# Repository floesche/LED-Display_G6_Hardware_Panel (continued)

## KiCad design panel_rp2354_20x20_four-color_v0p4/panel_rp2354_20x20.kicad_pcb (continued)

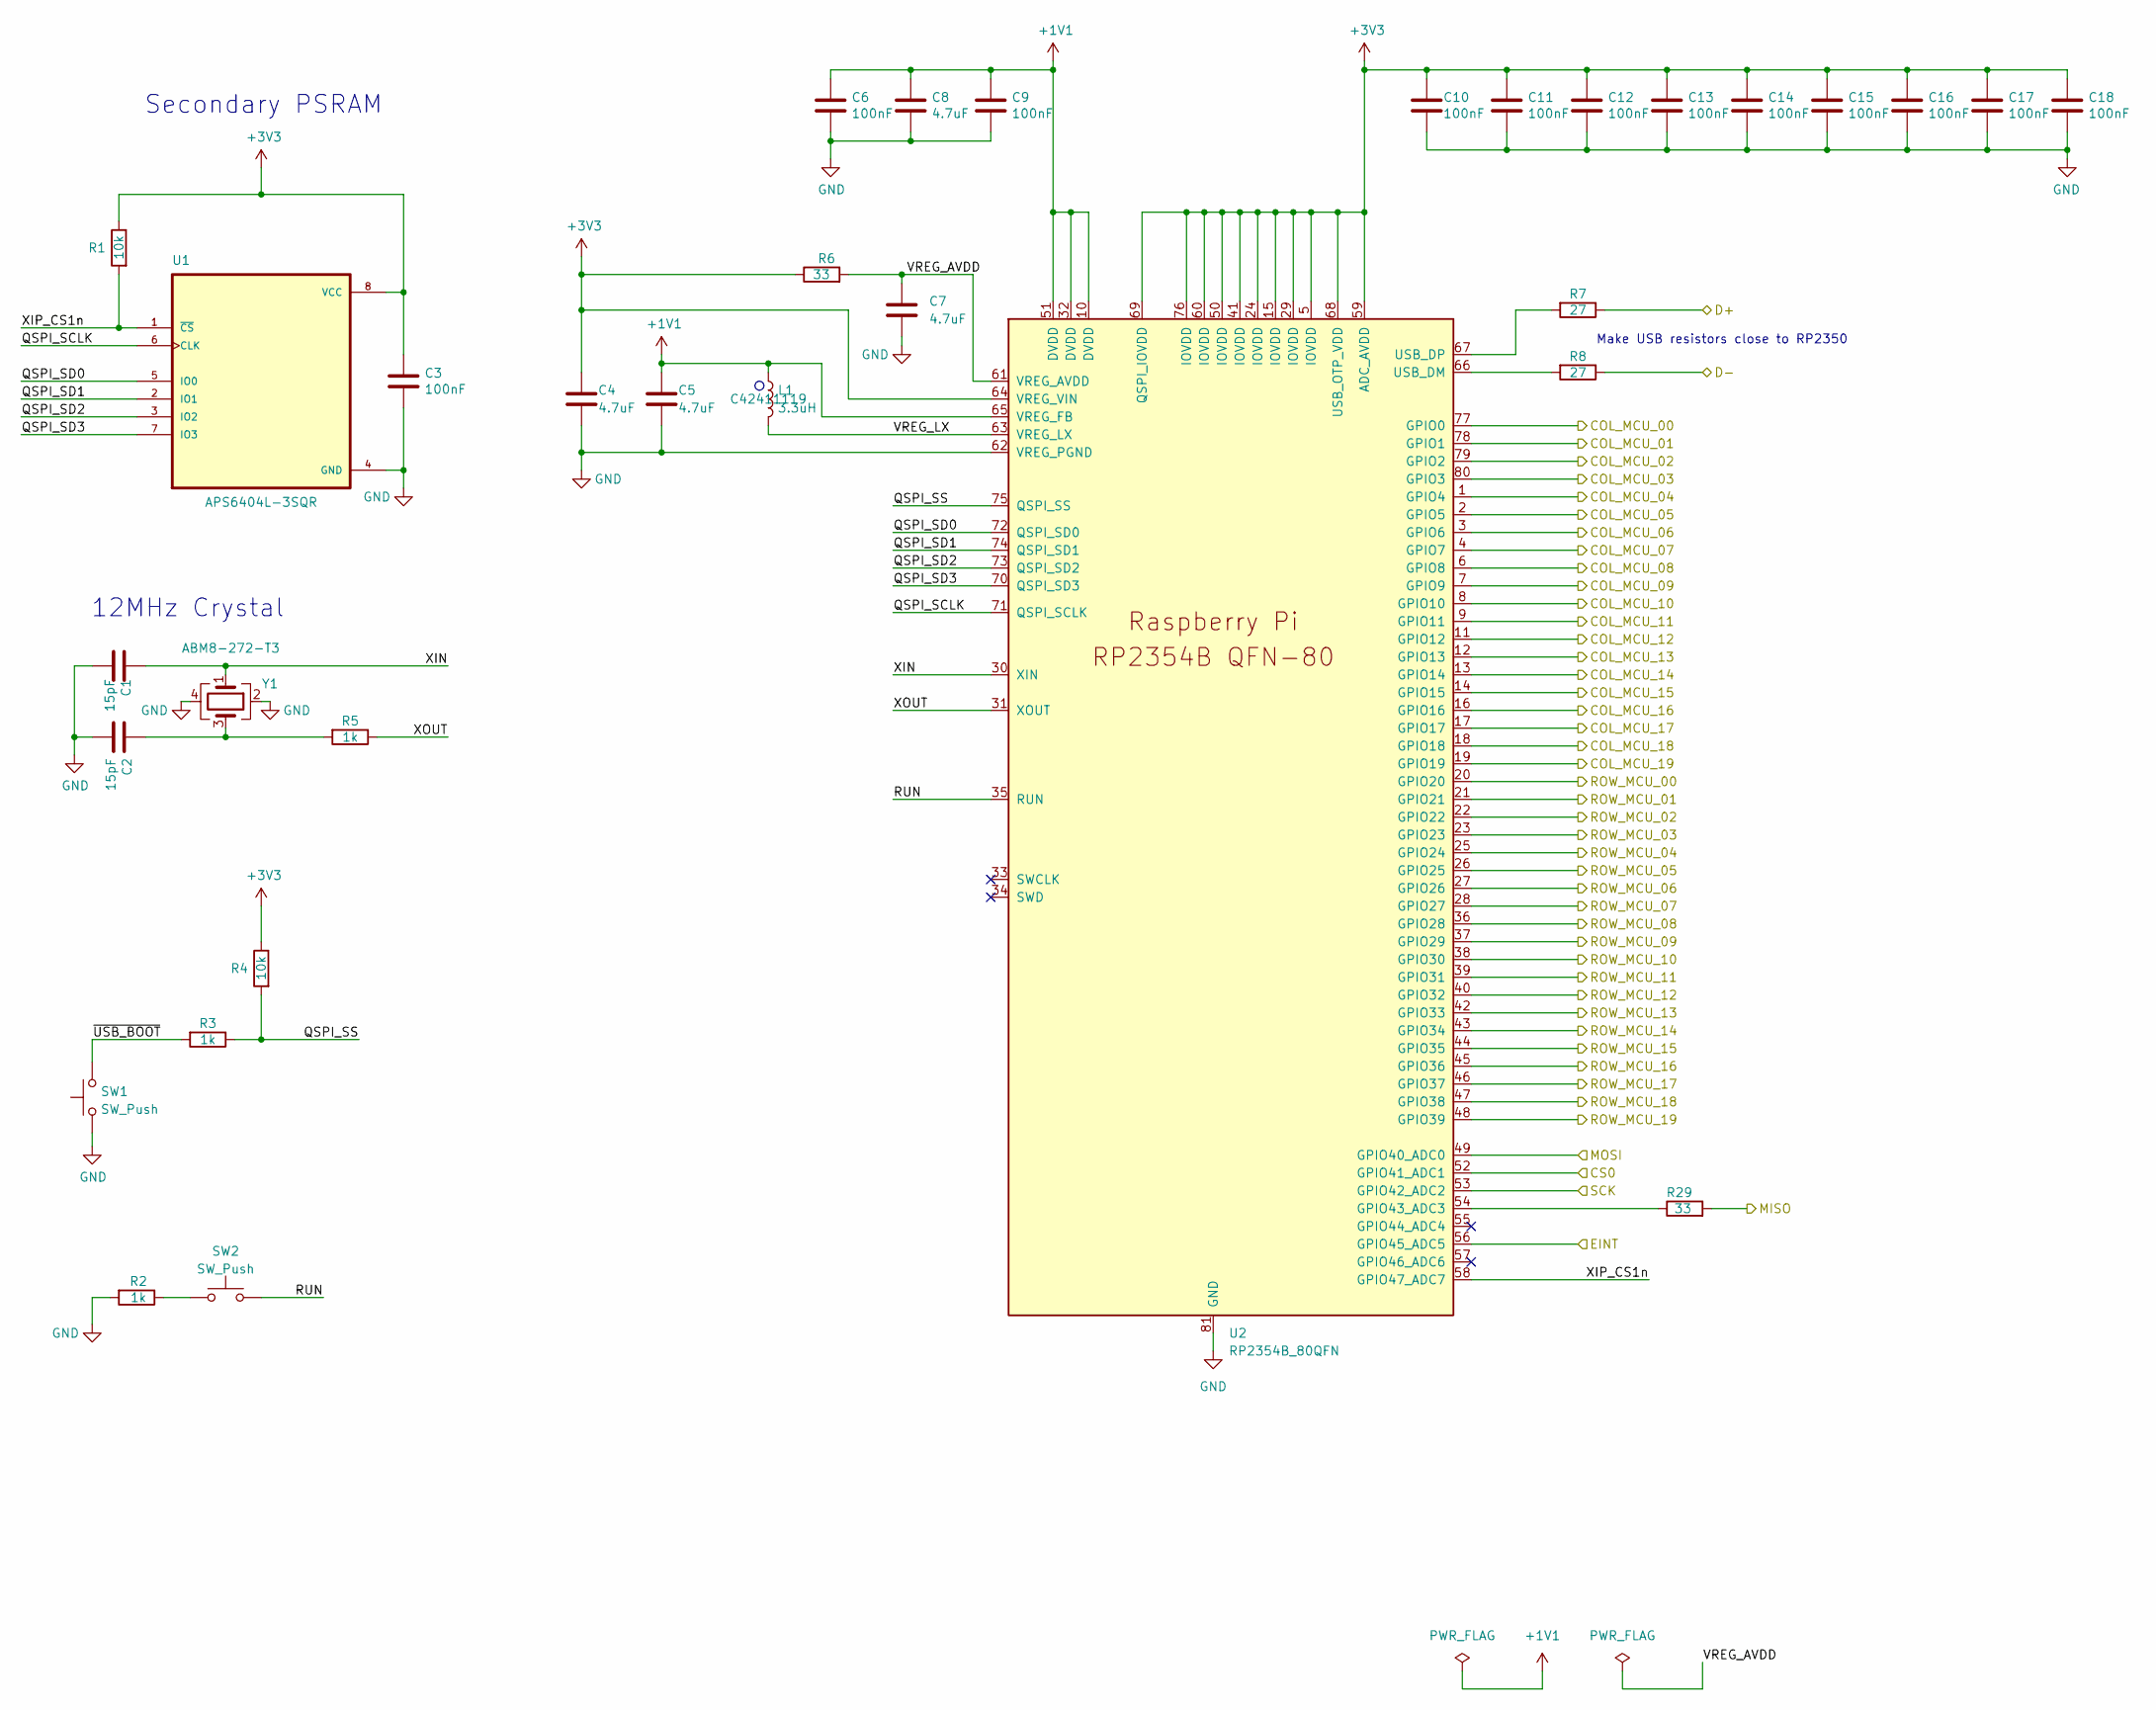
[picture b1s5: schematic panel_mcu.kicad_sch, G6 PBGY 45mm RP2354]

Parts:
C1, C2: 15pF; C_0201_0603Metric; LCSC Part # C541259
C3, C6, C9, C10, C11, C12, C13, C14, C15, C16, C17, C18: 100nF; C_0201_0603Metric; LCSC Part # C76939
C4, C5: 4.7uF; C_0402_1005Metric_small_pads; LCSC Part # C368809
C7, C8: 4.7uF; C_0402_1005Metric; LCSC Part # C368809
L1: 3.3uH; L_pol_2016; LCSC Part # C42411119
R1, R4: 10k; R_0201_0603Metric; LCSC Part # C473048
R2, R3, R5: 1k; R_0201_0603Metric; LCSC Part # C270365
R6, R29: 33; R_0201_0603Metric; LCSC Part # C295794
R7, R8: 27; R_0201_0603Metric; LCSC Part # C473051
SW1, SW2: SW_Push; TS-1088-AR02016; LCSC Part # C720477
U1: APS6404L-3SQR; flashmem_PSON50P300X200X60-9N; LCSC Part # C3040877
U2: RP2354B_80QFN; RP2350-QFN-80-1EP_10x10_P0.4mm_EP3.4x3.4mm_ThermalVias; LCSC Part # C39843328
Y1: ABM8-272-T3; Crystal_SMD_3225-4Pin_3.2x2.5mm; LCSC Part # C20625731

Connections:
+1V1: C5.1, C6.1, C8.1, C9.1, L1.1, U2.10 (DVDD), U2.32 (DVDD), U2.51 (DVDD), U2.65 (VREG_FB)
+3V3: C3.1, C4.1, C10.1, C11.1, C12.1, C13.1, C14.1, C15.1, C16.1, C17.1, C18.1, R1.1, R4.1, R6.1, U1.8 (VCC), U2.5 (IOVDD), U2.15 (IOVDD), U2.24 (IOVDD), U2.29 (IOVDD), U2.41 (IOVDD), U2.50 (IOVDD), U2.59 (ADC_AVDD), U2.60 (IOVDD), U2.64 (VREG_VIN), U2.68 (USB_OTP_VDD), U2.69 (QSPI_IOVDD), U2.76 (IOVDD); also elsewhere on the board
/drivers/COL_MCU_00: U2.77 (GPIO0); also elsewhere on the board
/drivers/COL_MCU_01: U2.78 (GPIO1); also elsewhere on the board
/drivers/COL_MCU_02: U2.79 (GPIO2); also elsewhere on the board
/drivers/COL_MCU_03: U2.80 (GPIO3); also elsewhere on the board
/drivers/COL_MCU_04: U2.1 (GPIO4); also elsewhere on the board
/drivers/COL_MCU_05: U2.2 (GPIO5); also elsewhere on the board
/drivers/COL_MCU_06: U2.3 (GPIO6); also elsewhere on the board
/drivers/COL_MCU_07: U2.4 (GPIO7); also elsewhere on the board
/drivers/COL_MCU_08: U2.6 (GPIO8); also elsewhere on the board
/drivers/COL_MCU_09: U2.7 (GPIO9); also elsewhere on the board
/drivers/COL_MCU_10: U2.8 (GPIO10); also elsewhere on the board
/drivers/COL_MCU_11: U2.9 (GPIO11); also elsewhere on the board
/drivers/COL_MCU_12: U2.11 (GPIO12); also elsewhere on the board
/drivers/COL_MCU_13: U2.12 (GPIO13); also elsewhere on the board
/drivers/COL_MCU_14: U2.13 (GPIO14); also elsewhere on the board
/drivers/COL_MCU_15: U2.14 (GPIO15); also elsewhere on the board
/drivers/COL_MCU_16: U2.16 (GPIO16); also elsewhere on the board
/drivers/COL_MCU_17: U2.17 (GPIO17); also elsewhere on the board
/drivers/COL_MCU_18: U2.18 (GPIO18); also elsewhere on the board
/drivers/COL_MCU_19: U2.19 (GPIO19); also elsewhere on the board
/drivers/ROW_MCU_00: U2.20 (GPIO20); also elsewhere on the board
/drivers/ROW_MCU_01: U2.21 (GPIO21); also elsewhere on the board
/drivers/ROW_MCU_02: U2.22 (GPIO22); also elsewhere on the board
/drivers/ROW_MCU_03: U2.23 (GPIO23); also elsewhere on the board
/drivers/ROW_MCU_04: U2.25 (GPIO24); also elsewhere on the board
/drivers/ROW_MCU_05: U2.26 (GPIO25); also elsewhere on the board
/drivers/ROW_MCU_06: U2.27 (GPIO26); also elsewhere on the board
/drivers/ROW_MCU_07: U2.28 (GPIO27); also elsewhere on the board
/drivers/ROW_MCU_08: U2.36 (GPIO28); also elsewhere on the board
/drivers/ROW_MCU_09: U2.37 (GPIO29); also elsewhere on the board
/drivers/ROW_MCU_10: U2.38 (GPIO30); also elsewhere on the board
/drivers/ROW_MCU_11: U2.39 (GPIO31); also elsewhere on the board
/drivers/ROW_MCU_12: U2.40 (GPIO32); also elsewhere on the board
/drivers/ROW_MCU_13: U2.42 (GPIO33); also elsewhere on the board
/drivers/ROW_MCU_14: U2.43 (GPIO34); also elsewhere on the board
/drivers/ROW_MCU_15: U2.44 (GPIO35); also elsewhere on the board
/drivers/ROW_MCU_16: U2.45 (GPIO36); also elsewhere on the board
/drivers/ROW_MCU_17: U2.46 (GPIO37); also elsewhere on the board
/drivers/ROW_MCU_18: U2.47 (GPIO38); also elsewhere on the board
/drivers/ROW_MCU_19: U2.48 (GPIO39); also elsewhere on the board
/panel_header/CS0: U2.52 (GPIO41_ADC1); also elsewhere on the board
/panel_header/EINT: U2.56 (GPIO45_ADC5); also elsewhere on the board
/panel_header/MISO: R29.2; also elsewhere on the board
/panel_header/MOSI: U2.49 (GPIO40_ADC0); also elsewhere on the board
/panel_header/SCK: U2.53 (GPIO42_ADC2); also elsewhere on the board
/panel_mcu/D+: R7.1; also elsewhere on the board
/panel_mcu/D-: R8.1; also elsewhere on the board
/panel_mcu/QSPI_SCLK: U1.6 (CLK), U2.71 (QSPI_SCLK)
/panel_mcu/QSPI_SD0: U1.5 (IO0), U2.72 (QSPI_SD0)
/panel_mcu/QSPI_SD1: U1.2 (IO1), U2.74 (QSPI_SD1)
/panel_mcu/QSPI_SD2: U1.3 (IO2), U2.73 (QSPI_SD2)
/panel_mcu/QSPI_SD3: U1.7 (IO3), U2.70 (QSPI_SD3)
/panel_mcu/QSPI_SS: R3.1, R4.2, U2.75 (QSPI_SS)
/panel_mcu/RUN: SW2.2, U2.35 (RUN)
/panel_mcu/VREG_AVDD: C7.1, R6.2, U2.61 (VREG_AVDD)
/panel_mcu/VREG_LX: L1.2, U2.63 (VREG_LX)
/panel_mcu/XIN: C1.1, U2.30 (XIN), Y1.1
/panel_mcu/XIP_CS1n: R1.2, U1.1 (~CS), U2.58 (GPIO47_ADC7)
/panel_mcu/XOUT: R5.1, U2.31 (XOUT)
/panel_mcu/~USB_BOOT: R3.2, SW1.2
GND: C1.2, C2.2, C3.2, C4.2, C5.2, C6.2, C7.2, C8.2, C9.2, C10.2, C11.2, C12.2, C13.2, C14.2, C15.2, C16.2, C17.2, C18.2, R2.2, SW1.1, U1.4 (GND), U2.62 (VREG_PGND), U2.81 (GND), Y1.2, Y1.4; also elsewhere on the board
unnamed: C2.1, R5.2, Y1.3
unnamed: R2.1, SW2.1
unnamed: R29.1, U2.54 (GPIO43_ADC3)
unnamed: R8.2, U2.66 (USB_DM)
unnamed: R7.2, U2.67 (USB_DP)

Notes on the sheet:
12MHz Crystal
Secondary PSRAM
Make USB resistors close to RP2350

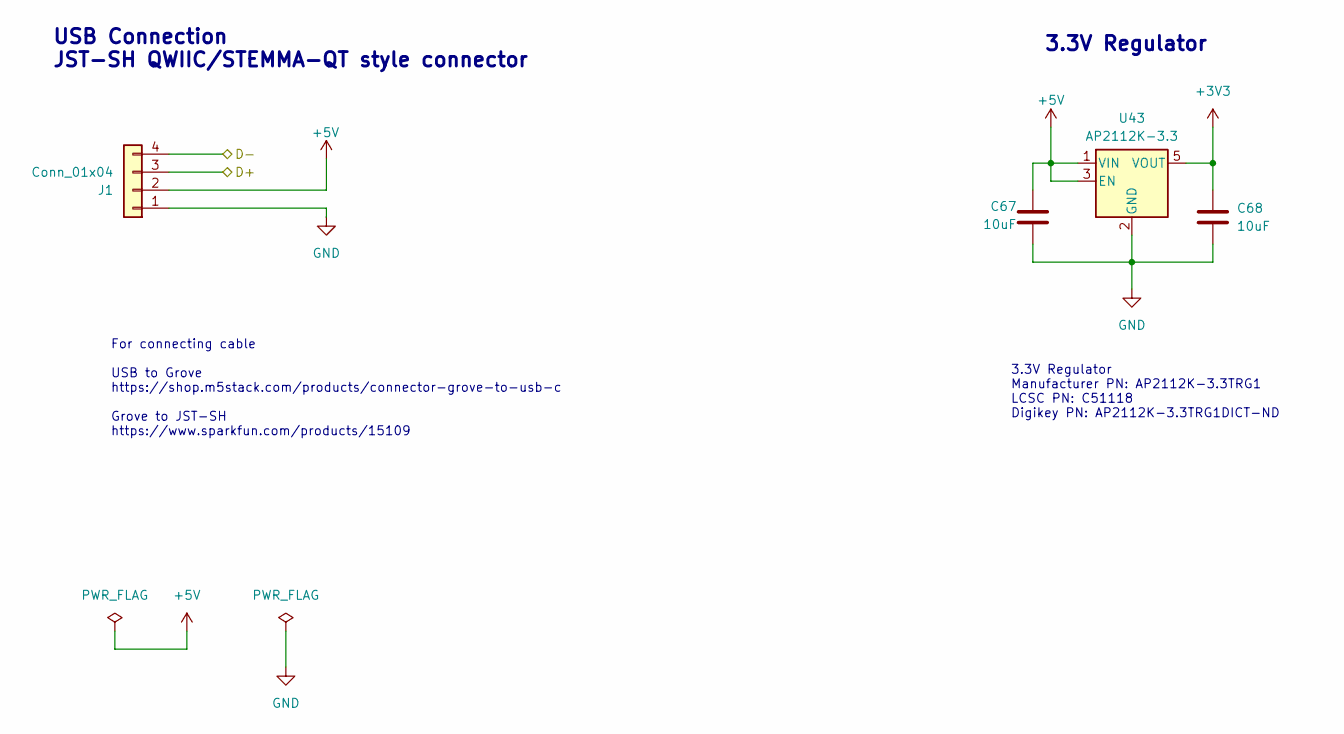
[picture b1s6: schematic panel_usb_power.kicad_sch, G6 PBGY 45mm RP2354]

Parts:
C67, C68: 10uF; C_0402_1005Metric; LCSC Part # C315248
J1: Conn_01x04; JST_SH_BM04B-SRSS-TB_1x04-1MP_P1.00mm_Vertical; LCSC Part # C160390
U43: AP2112K-3.3; SOT-23-5; LCSC Part # C51118

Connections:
+3V3: C68.1, U43.5 (VOUT); also elsewhere on the board
+5V: C67.1, J1.2, U43.1 (VIN), U43.3 (EN); also elsewhere on the board
/panel_mcu/D+: J1.3; also elsewhere on the board
/panel_mcu/D-: J1.4; also elsewhere on the board
GND: C67.2, C68.2, J1.1, U43.2 (GND); also elsewhere on the board

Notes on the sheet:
3.3V Regulator
For connecting cable USB to Grove https://shop.m5stack.com/products/connector-grove-to-usb-c Grove to JST-SH https://www.sparkfun.com/products/15109
USB Connection JST-SH QWIIC/STEMMA-QT style connector
3.3V Regulator Manufacturer PN: AP2112K-3.3TRG1 LCSC PN: C51118 Digikey PN: AP2112K-3.3TRG1DICT-ND

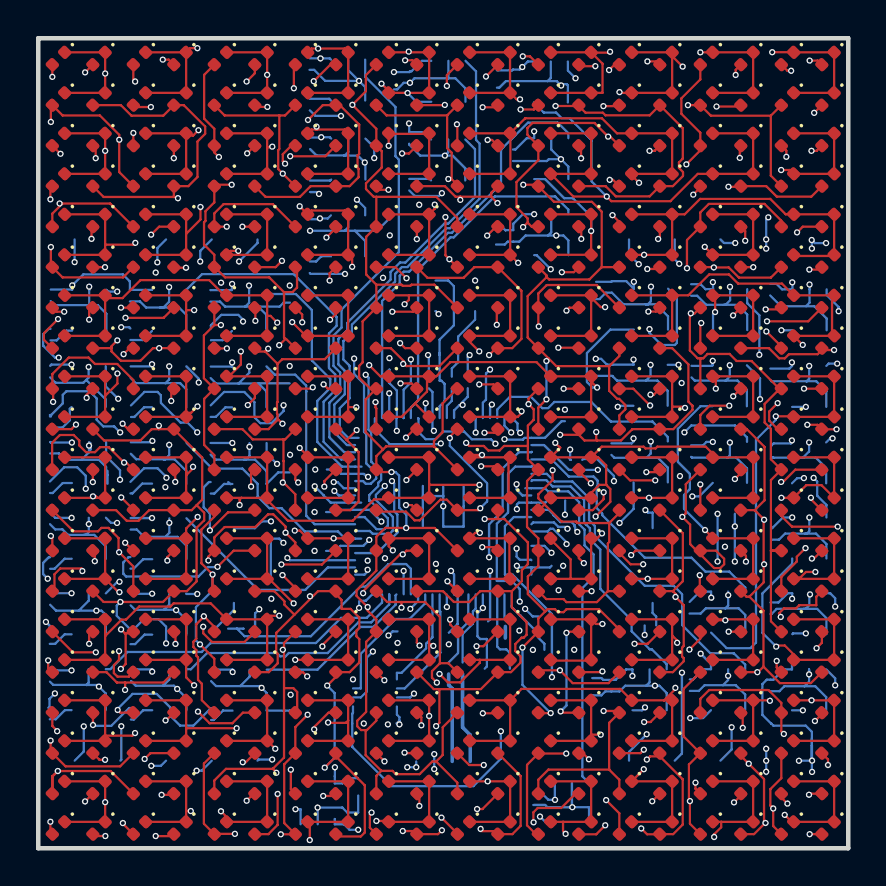
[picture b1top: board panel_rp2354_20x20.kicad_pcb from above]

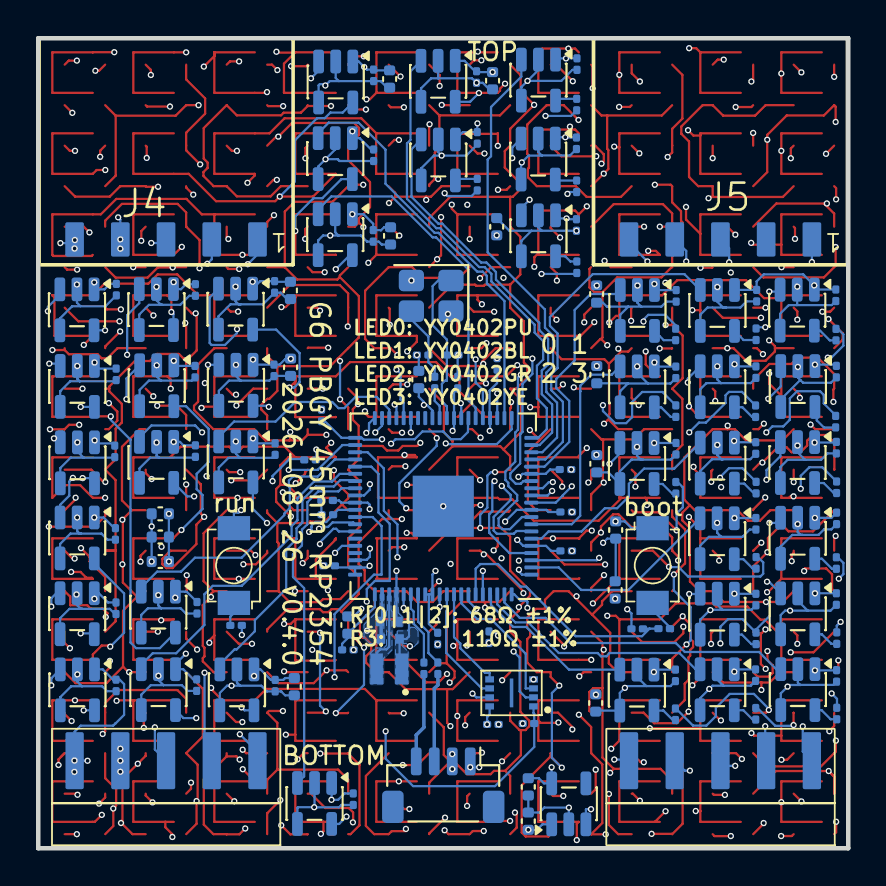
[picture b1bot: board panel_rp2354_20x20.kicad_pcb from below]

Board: 6 copper layers, 45.0 x 45.0 mm, 557 parts (157 on the bottom side), 132 nets.
